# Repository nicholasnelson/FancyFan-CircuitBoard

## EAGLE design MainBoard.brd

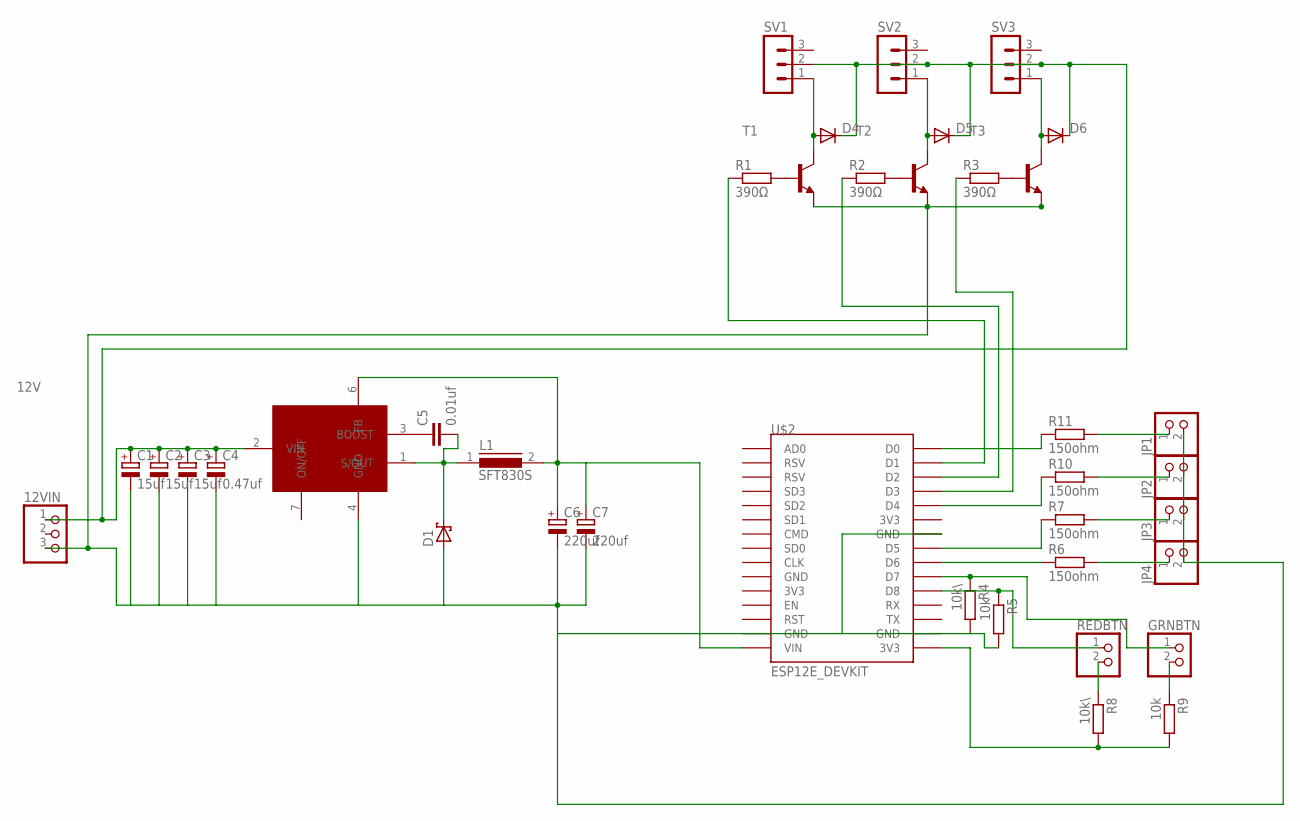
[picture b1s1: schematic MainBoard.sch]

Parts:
12VIN: PINHD-1X3; 1X03
C1, C2, C3: 15uf; E2,5-6E
C4: 0.47uf; E2,5-6E
C5: 0.01uf; C050-024X044
C6, C7: 220uf; E2,5-6E
D1: SCHOTTKY-DIODEC4111-15; C4111-15
D4, D5, D6: DIODE-D-2.5; D-2.5
GRNBTN: PINHD-1X2; 1X02
JP1, JP2, JP3, JP4: PINHD-1X2; 1X02
L1: SFT830S
R1, R2, R3: 390Ω; 0207/5V
R4, R8: 10k\; 0207/5V
R5, R9: 10k; 0207/5V
R6, R7, R10, R11: 150ohm; 0204V
REDBTN: PINHD-1X2; 1X02
SV1, SV2, SV3: MA03-1
T1, T2, T3: -NPN-TO92; TO92
U$1: LM2678T-5; TO-220
U$2: ESP12E_DEVKIT

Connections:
5V: C6.+, C7.+, L1.2, U$1.6 (FB), U$2.VIN
12V: 12VIN.1, C1.+, C2.+, C3.+, C4.+, D4.C, D5.C, D6.C, SV1.2, SV2.2, SV3.2, U$1.2 (VIN)
GND: 12VIN.3, C1.-, C2.-, C3.-, C4.-, C6.-, C7.-, D1.A, JP1.2, JP2.2, JP3.2, JP4.2, R4.2, R5.2, T1.1 (E), T2.1 (E), T3.1 (E), U$1.4 (GND), U$2.GND@1 (GND), U$2.GND@2 (GND), U$2.GND@3 (GND)
unnamed: R1.1, U$2.D1
unnamed: R2.1, U$2.D2
unnamed: D4.A, SV1.1, T1.3 (C)
unnamed: C5.2, D1.C, L1.1, U$1.1 (S/OUT)
unnamed: D5.A, SV2.1, T2.3 (C)
unnamed: C5.1, U$1.3 (BOOST)
unnamed: D6.A, SV3.1, T3.3 (C)
unnamed: R3.1, U$2.D3
unnamed: R1.2, T1.2 (B)
unnamed: R2.2, T2.2 (B)
unnamed: R3.2, T3.2 (B)
unnamed: R8.2, R9.2, U$2.3V3@2 (3V3)
unnamed: R8.1, REDBTN.2
unnamed: R11.1, U$2.D0
unnamed: R10.1, U$2.D4
unnamed: R7.1, U$2.D5
unnamed: R6.1, U$2.D6
unnamed: JP1.1, R11.2
unnamed: JP2.1, R10.2
unnamed: JP3.1, R7.2
unnamed: GRNBTN.2, R9.1
unnamed: R5.1, REDBTN.1, U$2.D8
unnamed: GRNBTN.1, R4.1, U$2.D7
unnamed: JP4.1, R6.2

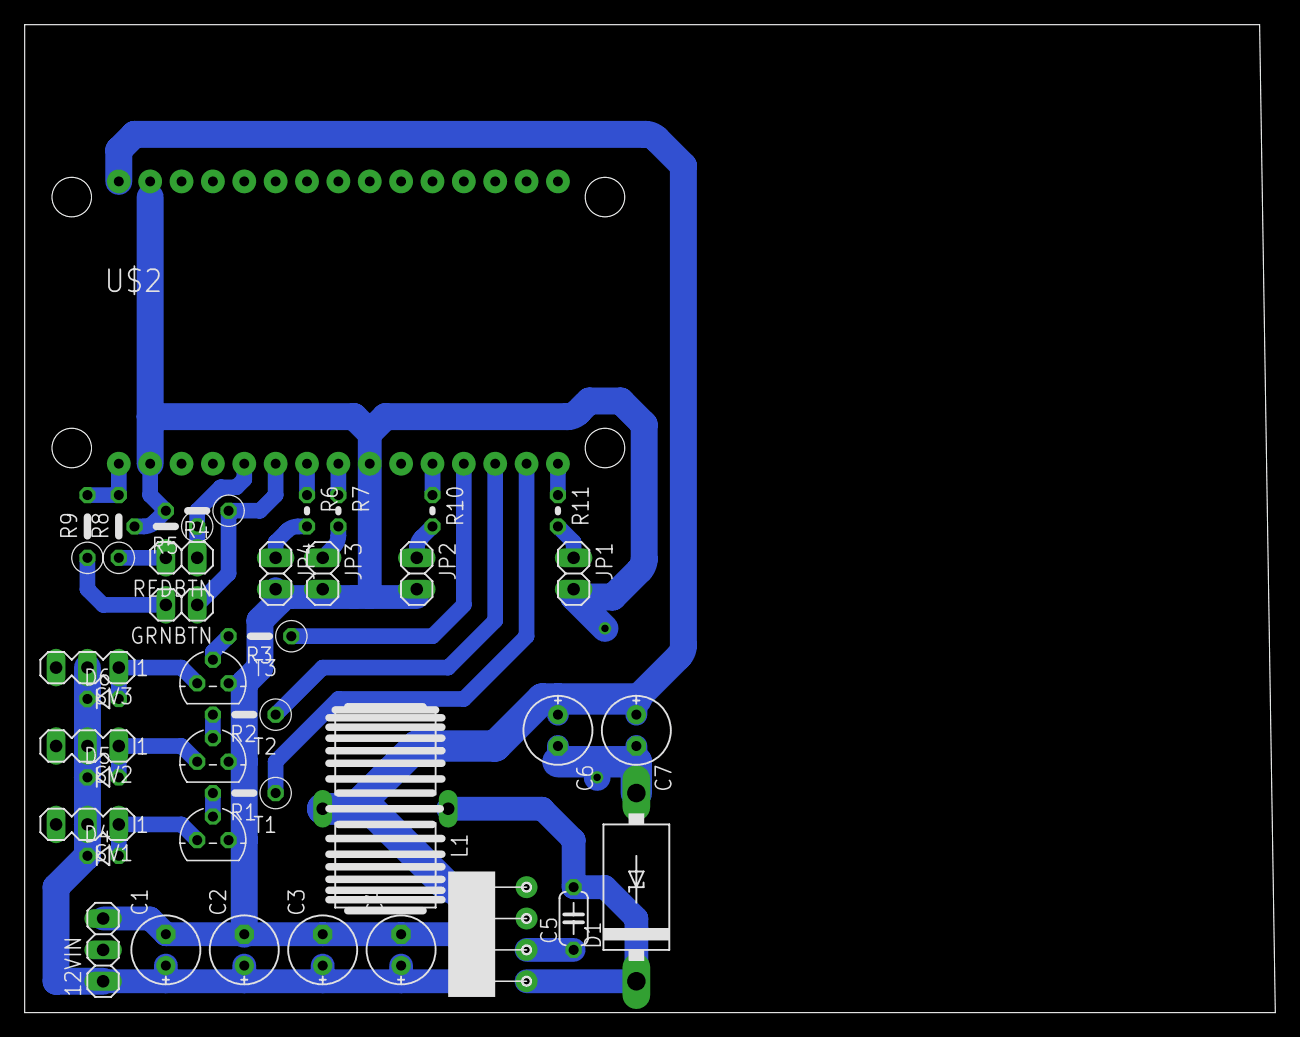
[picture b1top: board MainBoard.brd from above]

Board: 2 copper layers, 101.3 x 80.0 mm, 38 parts (0 on the bottom side), 27 nets.

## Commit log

2017-01-19 :circus_tent: Added .gitattributes
2017-01-19 Add schematic and board files
    This is the initial version of the control board including a switching
    power supply
